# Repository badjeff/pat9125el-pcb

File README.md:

# PAT9125EL PCB

[PixArt PAT9125EL-TKIT / TKMT](https://www.pixart.com/products-detail/72/PAT9125EL-TKIT___TKMT) low power optical tracking sensor breakout board.

- Be operated with 3.3V voltage level ONLY.
- Outlined as narrow as possible for side mount horizontally and perpendicular on low profile keyboards.

*Figure 1: Size comparing to Seeed XIAO BLE*

## PCB

Online preview avaliable [here](https://kicanvas.org/?github=https%3A%2F%2Fgithub.com%2Fbadjeff%2Fpat9125el-pcb), powered by [KiCanvas](https://github.com/theacodes/kicanvas).

*Figure 2: PCB edgecuts dimension*

*Figure 3: PCB 3D View - 1.6mm FR4*

### BOM

|Designator|Footprint|Quantity|Value|LCSC Part #|
|-|-|-|-|-|
|C1|SMD 0402|1|100nF||
|C2|SMD 0402|1|10uF||
|C3|SMD 0402|1|4.7uF||
|R1, R2|SMD 0402|1|5K||
|U1|PAT9125EL|1|PAT9125EL-TKIT / TKMT||
|J1|1.27mm Pin header|1|1x6||

- SMD 0402 (Imperial) aka 1005 Metric.

### Board Characteristics

- Copper layer count: 2
- Board thickness: 1.6 mm or 1.2 mm or 1.0 mm
- Board overall dimensions: 4.825 x 8.9 mm

### Voltage level config

- 3.3V logic
- VIN: 3.3V

## License

Available under the [CERN-OHL-P v2](/LICENSE) permissive license.

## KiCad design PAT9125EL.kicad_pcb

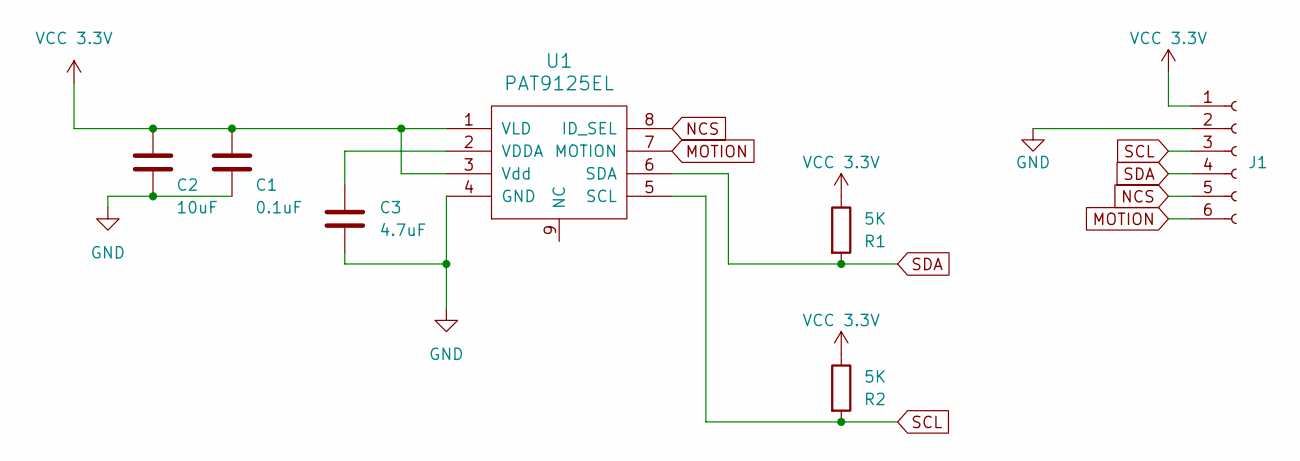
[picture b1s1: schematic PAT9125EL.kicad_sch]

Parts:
C1: 0.1uF; C_0402_1005Metric
C2: 10uF; C_0402_1005Metric
C3: 4.7uF; C_0402_1005Metric
J1: Conn_01x06_Socket; PinHeader_1x06_P1.27mm_Vertical
R1, R2: 5K; R_0402_1005Metric
U1: PAT9125EL

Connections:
GND: C1.2, C2.2, C3.2, J1.2, U1.4 (GND)
MOTION: J1.6, U1.7 (MOTION)
NCS: J1.5, U1.8 (ID_SEL)
unnamed: C3.1, U1.2 (VDDA)
SCL: J1.3, R2.2, U1.5 (SCL)
SDA: J1.4, R1.2, U1.6 (SDA)
VCC 3.3V: C1.1, C2.1, J1.1, R1.1, R2.1, U1.1 (VLD), U1.3 (Vdd)

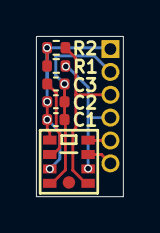
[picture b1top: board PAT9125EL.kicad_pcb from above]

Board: 2 copper layers, 4.8 x 8.9 mm, 7 parts (0 on the bottom side), 7 nets.

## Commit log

2025-11-01 init commit
2025-11-01 add README.md
2025-11-09 add photo-1
2025-11-13 shorten 1.5mm
2025-11-15 add panelized pcb
2025-11-20 add photo-1.jpg
